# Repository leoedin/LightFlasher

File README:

The Light Flasher code and EAGLE CAD designs. See [Leo Rampen's Website](http://lrampen.com) for more.

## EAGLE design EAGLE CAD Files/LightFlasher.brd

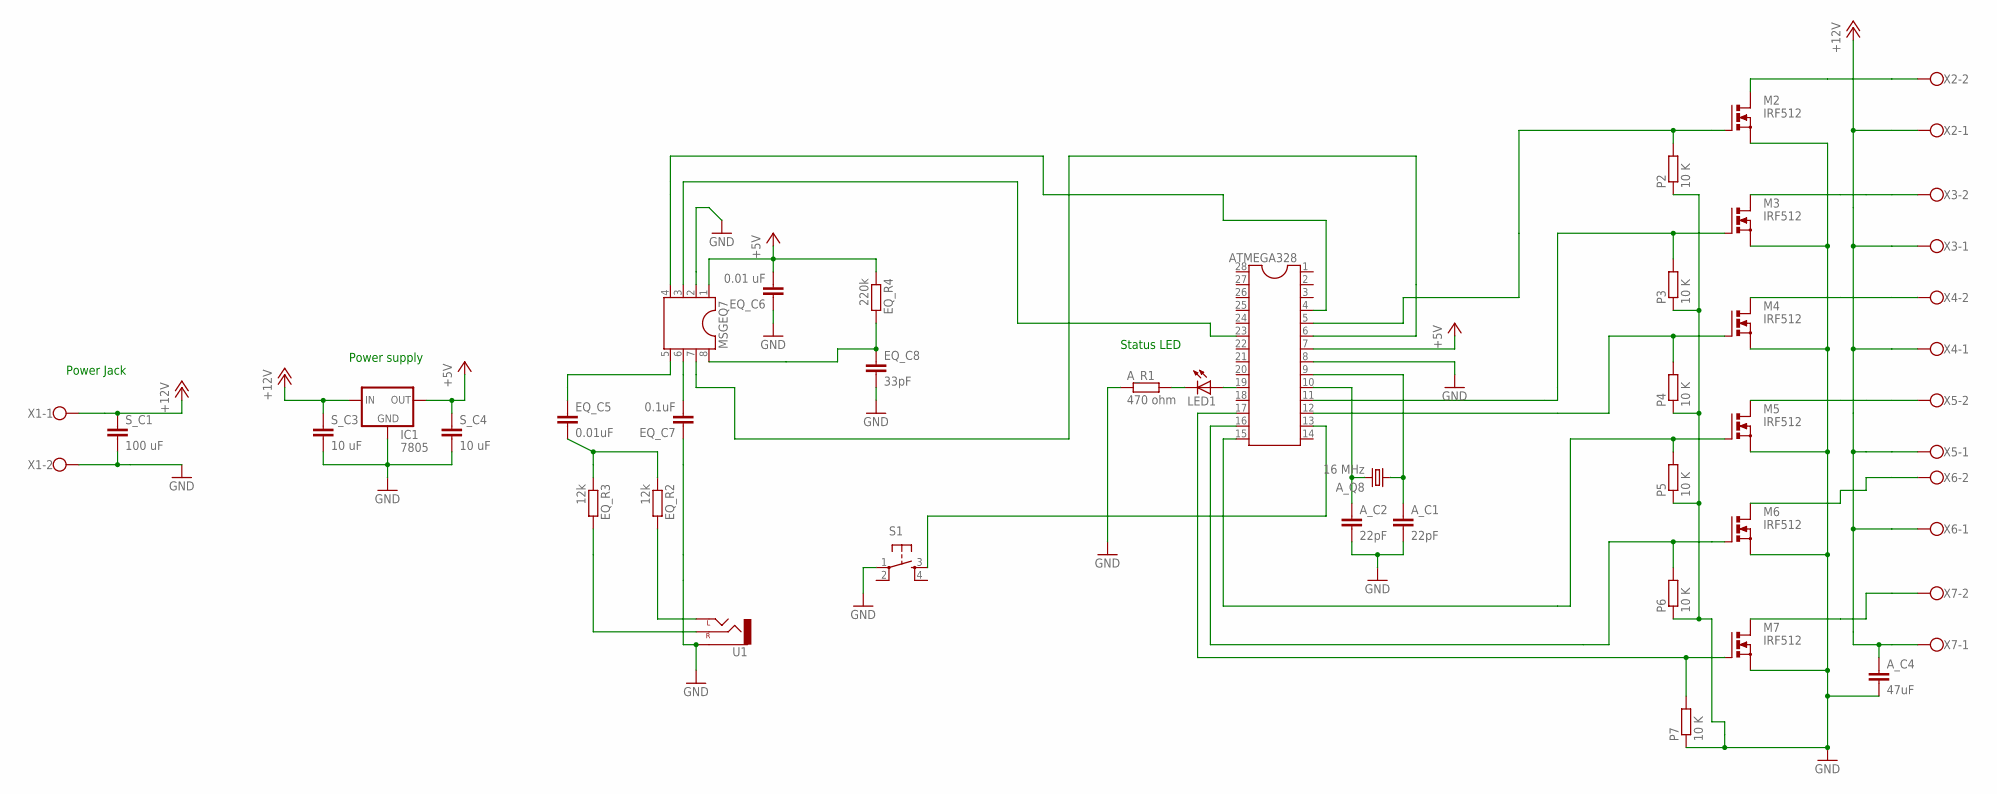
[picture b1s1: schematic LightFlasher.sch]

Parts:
ATMEGA328: DIL28-3
A_C1: 22pF; C025-024X044
A_C2: 22pF; C050-030X075
A_C4: 47uF; C025-025X050
A_Q8: 16 MHz; HC49/S
A_R1: 470 ohm; 0204/5
EQ_C5: 0.01uF; C025-024X044
EQ_C6: 0.01 uF; C025-024X044
EQ_C7: 0.1uF; C025-024X044
EQ_C8: 33pF; C025-024X044
EQ_R2, EQ_R3: 12k; 0204/5
EQ_R4: 220k; 0204/5
IC1: 7805; 78XXS
LED1: LED3MM
M2, M3, M4, M5, M6, M7: IRF512; TO220BV
MSGEQ7: DIL8S; SOCKET-08
P2, P3, P4, P5, P6, P7: 10 K; 0204/5
S1: TAC_SWITCHPTH; TACTILE-PTH
S_C1: 100 uF; C050-025X075
S_C3, S_C4: 10 uF; C025-024X044
U1: AUDIO-JACKPTH; AUDIO-JACK
X1, X2, X3, X4, X5, X6, X7: W237-102

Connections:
+5V: ATMEGA328.7, EQ_C6.2, EQ_R4.1, IC1.OUT, MSGEQ7.1, S_C4.1
+12V: A_C4.1, IC1.IN, S_C1.1, S_C3.1, X1.1, X2.1, X3.1, X4.1, X5.1, X6.1, X7.1
GND: ATMEGA328.8, A_C1.2, A_C2.2, A_C4.2, A_R1.1, EQ_C6.1, EQ_C7.1, EQ_C8.2, IC1.GND, M2.S, M3.S, M4.S, M5.S, M6.S, M7.S, MSGEQ7.2, P2.1, P3.1, P4.1, P5.1, P6.1, P7.1, S1.1, S_C1.2, S_C3.2, S_C4.2, U1.SLEEVE, X1.2
M6: M6.D, X6.2
unnamed: ATMEGA328.10, A_C2.1, A_Q8.2
unnamed: ATMEGA328.9, A_C1.1, A_Q8.1
unnamed: ATMEGA328.19, LED1.A
unnamed: A_R1.2, LED1.K (C)
unnamed: EQ_R2.2, U1.TIP (LEFT)
unnamed: EQ_R3.2, U1.RING (RIGHT)
unnamed: ATMEGA328.17, M7.G, P7.2
unnamed: EQ_C5.1, MSGEQ7.5
unnamed: ATMEGA328.16, M6.G, P6.2
unnamed: ATMEGA328.4, MSGEQ7.4
unnamed: EQ_C7.2, MSGEQ7.6
unnamed: ATMEGA328.13, S1.3
unnamed: EQ_C8.1, EQ_R4.2, MSGEQ7.8
unnamed: ATMEGA328.23, MSGEQ7.3
unnamed: ATMEGA328.5, M2.G, P2.2
unnamed: ATMEGA328.11, M3.G, P3.2
unnamed: ATMEGA328.12, M4.G, P4.2
unnamed: ATMEGA328.15, M5.G, P5.2
unnamed: M4.D, X4.2
unnamed: M2.D, X2.2
unnamed: M7.D, X7.2
unnamed: M5.D, X5.2
unnamed: M3.D, X3.2
unnamed: EQ_C5.2, EQ_R2.1, EQ_R3.1
unnamed: ATMEGA328.6, MSGEQ7.7

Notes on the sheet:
Power supply
Status LED
Power Jack

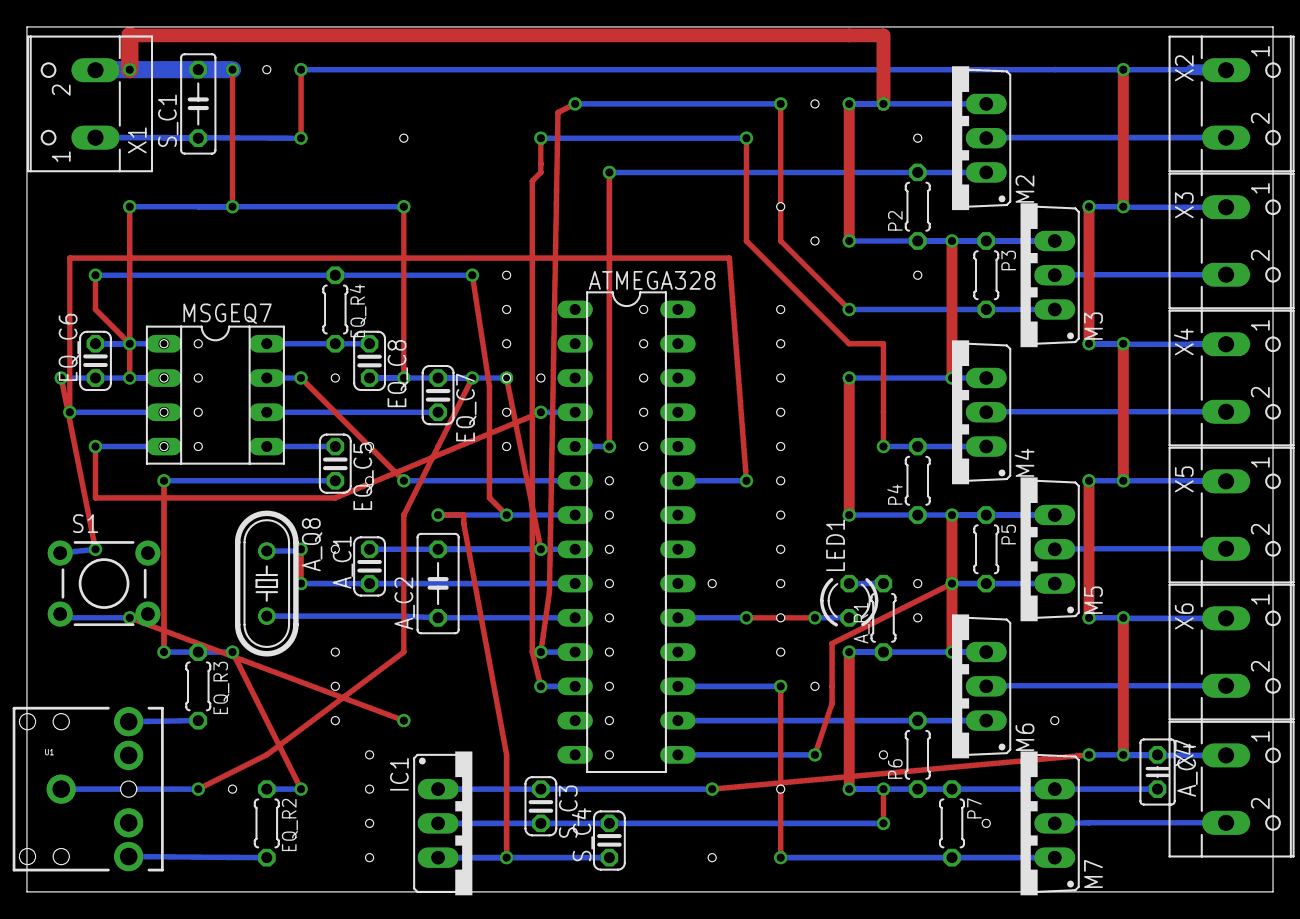
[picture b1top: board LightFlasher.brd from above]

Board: 2 copper layers, 92.4 x 64.1 mm, 40 parts (0 on the bottom side), 29 nets.

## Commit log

2012-05-08 updated arduino code
2012-05-08 added EAGLE CAD files
2012-05-08 removed old file
2012-05-08 fixed rights message

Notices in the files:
parts and their libraries:
SparkFun: Licensing: CC v3.0 Share-Alike You are welcome to use this library for commercial purposes.
